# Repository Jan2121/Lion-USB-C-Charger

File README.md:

# Lion-Schutz
The goal of this PCB is to power small uC based projects with Lithium Ion Batterys. for that purpose there is a USB-C charger an Lion protection ICs and an dcdc for a stable output voltage on board.
This is a hobby electronics project.

The PCB is designed to:
- generate a stable 3.3V rail,
- monitor overvoltage and undervoltage conditions,
- and charge a Li-Ion battery via USB-C.

## Used Chips

- TP4056
- DW01A
- TPS631000

## Expected Current Draw
If the PCB is connected to a battery only.
TP4056 -> 2uA
DW01A -> 3uA
TPS631000 -> 8uA 
Resistor devider -> 5uA
Total -> 18uA 

## Current Status

This version has been ordered and has not been tested yet.

## Render

## Schematic

[Open schematic PDF](Schmetaic.pdf)

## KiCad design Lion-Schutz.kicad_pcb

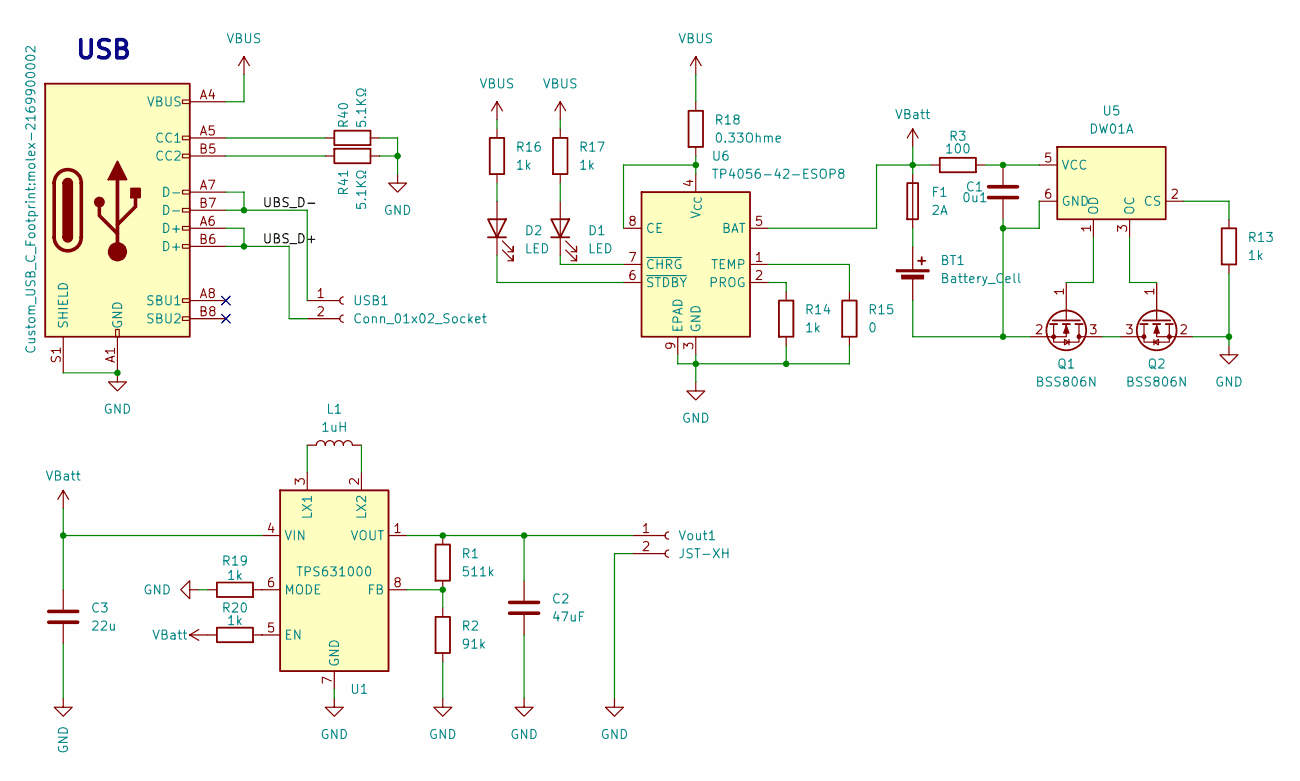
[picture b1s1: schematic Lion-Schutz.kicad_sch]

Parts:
BT1: Battery_Cell; JST_XH_S2B-XH-A_1x02_P2.50mm_Horizontal
C1: 0u1; C_0603_1608Metric_Pad1.08x0.95mm_HandSolder
C2: 47uF; C_0805_2012Metric_Pad1.18x1.45mm_HandSolder
C3: 22u; C_0603_1608Metric_Pad1.08x0.95mm_HandSolder
D1, D2: LED; C_0603_1608Metric_Pad1.08x0.95mm_HandSolder
F1: 2A; Fuse_0603_1608Metric_Pad1.05x0.95mm_HandSolder
J1: USB_C; molex-2169900002
L1: 1uH; L_1008_2520Metric_Pad1.43x2.20mm_HandSolder
Q1, Q2: BSS806N; SOT-23-3
R1: 511k; R_0603_1608Metric_Pad0.98x0.95mm_HandSolder
R2: 91k; R_0603_1608Metric_Pad0.98x0.95mm_HandSolder
R3: 100; R_0603_1608Metric_Pad0.98x0.95mm_HandSolder
R13, R14, R16, R17, R19, R20: 1k; R_0603_1608Metric_Pad0.98x0.95mm_HandSolder
R15: 0; R_0603_1608Metric_Pad0.98x0.95mm_HandSolder
R18: 0.33Ohme; R_1206_3216Metric_Pad1.30x1.75mm_HandSolder
R40, R41: 5.1KΩ; R_0603_1608Metric_Pad0.98x0.95mm_HandSolder; LCSC C25905
U1: TPS631000; SOT-583-8
U5: DW01A; SOT-23-6
U6: TP4056-42-ESOP8; SOIC-8-1EP_3.9x4.9mm_P1.27mm_EP2.41x3.3mm_ThermalVias
USB1: Conn_01x02_Socket; PinHeader_1x02_P2.54mm_Vertical
Vout1: JST-XH; JST_XH_S2B-XH-A_1x02_P2.50mm_Horizontal

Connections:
/UBS_D+: J1.A6 (D+), J1.B6 (D+), USB1.2
/UBS_D-: J1.A7 (D-), J1.B7 (D-), USB1.1
GND: C2.1, C3.1, J1.A1 (GND), J1.A12 (GND), J1.B1 (GND), J1.B12 (GND), J1.S1 (SHIELD), Q2.2 (S), R2.2, R13.2, R14.2, R15.2, R19.1, R40.2, R41.1, U1.7 (GND), U6.3 (GND), U6.9 (EPAD), Vout1.2
unnamed: BT1.1 (+), F1.2
unnamed: BT1.2 (-), C1.2, Q1.2 (S), U5.6 (GND)
unnamed: D1.2 (A), R17.2
unnamed: D1.1 (K), U6.7 (~CHRG)
unnamed: D2.2 (A), R16.2
unnamed: D2.1 (K), U6.6 (~STDBY)
unnamed: J1.A5 (CC1), R40.1
unnamed: J1.B5 (CC2), R41.2
unnamed: Q1.3 (D), Q2.3 (D)
unnamed: Q1.1 (G), U5.1 (OD)
unnamed: Q2.1 (G), U5.3 (OC)
unnamed: R20.2, U1.5 (EN)
unnamed: R1.2, R2.1, U1.8 (FB)
unnamed: L1.1, U1.3 (LX1)
unnamed: L1.2, U1.2 (LX2)
unnamed: R19.2, U1.6 (MODE)
unnamed: C2.2, R1.1, U1.1 (VOUT), Vout1.1
unnamed: R13.1, U5.2 (CS)
unnamed: C1.1, R3.2, U5.5 (VCC)
unnamed: R18.2, U6.4 (V_{CC}), U6.8 (CE)
unnamed: R14.1, U6.2 (PROG)
unnamed: R15.1, U6.1 (TEMP)
VBUS: J1.A4 (VBUS), J1.A9 (VBUS), J1.B4 (VBUS), J1.B9 (VBUS), R16.1, R17.1, R18.1
VBatt: C3.2, F1.1, R3.1, R20.1, U1.4 (VIN), U6.5 (BAT)

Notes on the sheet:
USB

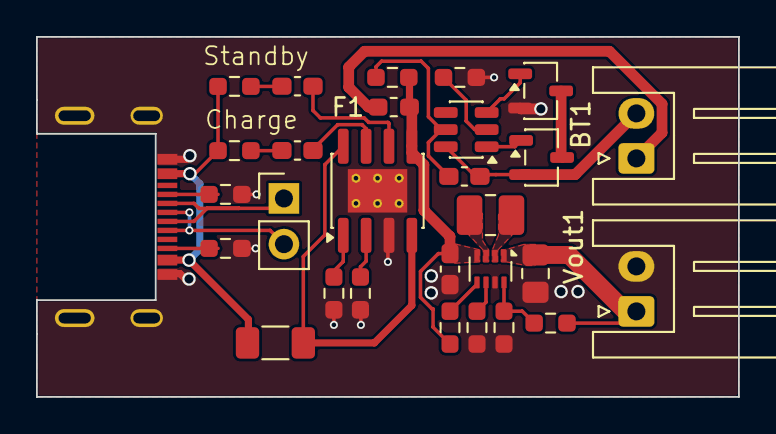
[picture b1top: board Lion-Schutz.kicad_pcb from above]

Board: 2 copper layers, 39.0 x 20.0 mm, 29 parts (0 on the bottom side), 27 nets.

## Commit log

2026-03-29 First Prototype
2026-03-29 Added README
2026-03-29 Added expected Power Draw to the README
2026-03-29 Update project description in README.md
    Clarify the goal of the Lion-Schutz PCB project.
